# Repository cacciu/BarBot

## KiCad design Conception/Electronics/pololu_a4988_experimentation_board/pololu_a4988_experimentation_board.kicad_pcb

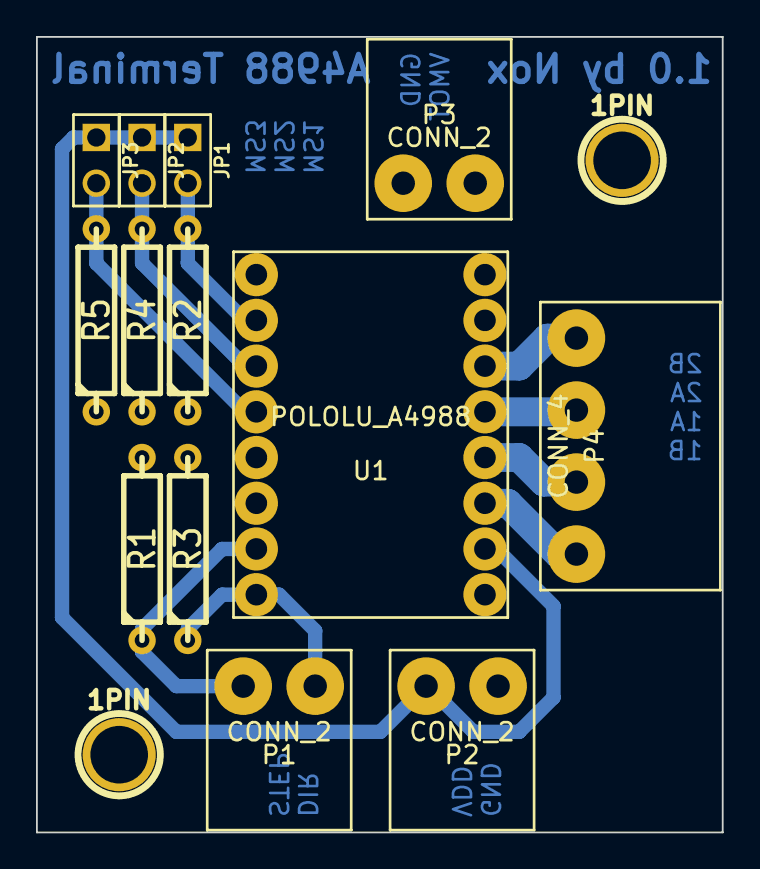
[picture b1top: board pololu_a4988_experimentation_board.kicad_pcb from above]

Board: 2 copper layers, 38.1 x 44.2 mm, 16 parts (1 on the bottom side), 12 nets.

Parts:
1PIN, 1PIN#2: P***; 1pin
C1: CP1; SMDSVP10
JP1, JP2, JP3: JUMPER; PIN_ARRAY_2X1
P1, P2, P3: CONN_2; Terminal2
P4: CONN_4; Terminal-4
R1, R2, R3, R4, R5: R; R4
U1: POLOLU_A4988; Pololu_A4988

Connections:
+24V: C1.1, P3.2, U1.16
GND: C1.2, P2.1, P3.1, R1.2, R2.1, R3.2, R4.1, R5.1, U1.1, U1.5, U1.6, U1.9, U1.15
unnamed: P4.2, U1.13
unnamed: P4.4, U1.11
unnamed: P4.3, U1.12
unnamed: P4.1, U1.14
unnamed: P1.1, R3.1, U1.8
unnamed: P1.2, R1.1, U1.7
unnamed: JP1.2, R2.2, U1.2
unnamed: JP3.2, R5.2, U1.4
unnamed: JP2.2, R4.2, U1.3
VDD: JP1.1, JP2.1, JP3.1, P2.2, U1.10

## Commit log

2015-04-28 Add first draft
2015-04-28 Add Readme
2015-07-05 Add Pump and Cup Dispenser Sketch
2015-07-06 Add tolerance for 3D printer
2015-07-06 Adapt Cup_Dispenser tolerances
2015-07-06 Adapt Hull to be better printable.
2015-07-06 Adapt 3d printing
2015-07-06 Adaption
2015-07-07 Add Slider Cover
2015-07-08 Adapt Hull to be easy printable
2015-07-09 Add a more dynamic version of Cup_Dispenser
2015-07-09 Add adaptive Cup Dispenser version
    Add new adaptive design for a wide span of cup sizes
2015-07-09 Adapt slider to include small chamfer on first ring
2015-07-12 Adapt Cup Dispenser slider to not squeeze cup
2015-07-13 Fix dependencies in Cup Dispenser
2015-07-14 Fix sizes, add board to cup dispenser
2015-07-14 Adapt pump adapter for servo test
2015-07-14 Adapt Pump Axes Adapter Holes
2015-07-15 Adapt hole sizes in Cup Designer, adapt axes
2015-07-16 Adapt Cup Dispenser Transmission Cage height
2015-07-17 Add chamfer for easy cup dispensing
2015-07-17 add bevel to slider separator
2015-07-17 Increase inner radius for better separation
2015-07-17 Increase only separator radius, chamfer on other ring
2015-07-19 Adapt Holes, Adapt Mount fixation point
2015-07-19 Add new cup dispenser concept
2015-07-20 Finish third gen cup dispenser design
2015-07-24 Add cutouts for wires to cup dispenser 3
2015-07-24 Add skrew hole to transmission
2015-07-24 Add Hull correction
2015-07-25 Resize the fixture for the PVC pipe
2015-07-29 Add Board Shape to Cup Dispenser
2015-07-29 Add Microswitch and LED holes to Cup Dispenser
2015-07-29 Resize RGB LED hole
2015-07-29 Redesign pump adapater, add chamfer to cup dispenser transmission
2015-07-29 Export STLs
2015-07-29 Add PCB project
2015-07-29 Fix bevel in cup dispenser transsmission
2015-07-30 Adaptable Pump Adapter Block
2015-07-30 Add Chamfer to Pump adapter block skrew holes
2015-07-30 Add chamfer to central axis of pump transmission
2015-07-30 Add Noah stuff
2015-07-30 Export STL
2015-07-31 Reduce tolerance of axis adapter
2015-07-31 Update Board
2015-08-03 Adapt cup dispenser board
    TODO:
    - motor connector
    - sensor (diodes, micro switch)
    -pulldowns for LED-driver connectors
2015-08-03 Update Axis and Transmission
2015-08-03 Widen transmission hole size. Bevel for more stability into projected form
2015-08-05 Adapt for Nema 11
2015-08-05 Adapt Board Cutout to include cable relaxation
2015-08-05 Finished schematics for cup dispenser board
    TODO:
    - route board
2015-08-08 Should be final schematic
    CHANGES:
    - added fill meter diode and endstop to connector bus
    - changed connector to wurth
    - started routing
    TODO:
    - route board
2015-08-09 Adapt Axis Adapter for better parametrization
2015-08-09 Adapt cup dispenser for nema 11 height. Add LED shift register stripe
2015-08-09 Cup Dispenser Fixture Montage larger
2015-08-09 Constrain to ground
2015-08-18 Add Transmission Nema 11 cut
2015-08-18 Widen Axis radius of transmission
2015-08-20 Fix transmission alignment
2015-08-20 Fix Hull alignment
2015-09-01 Update Board Layout
2015-09-01 Update Cup Dispenser Parts
2015-09-01 Update Cup Dispenser Parts 2
2015-10-01 Added basic firmware for CupDispenser board
2015-11-28 added PDF schematic for cup despenser board
2015-11-29 initial conept for ice dispenser, ready to print first parts A B
    A
2015-11-29 adding feed pipe for circular dispenser, minor fixes for main part
2016-01-04 added stray files for ice dispenser
2016-01-04 added one more lost file
2016-03-11 started test with auger style ice dispenser, parts are printing
2016-03-24 auger based ice dispenser elements resized for mounting inside 70mm tube
2016-04-08 Add ice crusher
2016-04-08 Add crusher claw step export
2016-04-08 Add new presentation
2016-04-12 Add Döme
2016-04-12 Adapt ice crusher
2016-04-15 Add new frame design
2016-04-26 New bigger crusher design
2016-04-29 First Scetch of the Barbot design
2016-05-03 Design: Minor Assembly changes
2016-05-10 Added Pump 3d model
2016-05-10 support arc
2016-05-13 Add a first draft of the sugardispenser.
    Use a screw conveyor-design to allow continuous
    dispension.
2016-05-23 TopArc Added
2016-05-24 Steckverbingungen und Assembly anpassungen
2016-05-26 Inventor Files converted to NX
2016-05-27 Pump parts fully converted to NX
2016-06-04 Pumpen Befestigung Kühlung
2016-10-31 Minor Arc inprovments, Pump Assembly
    hey
2016-11-15 The Brain
    half way done
2016-11-15 Start mit dem CAD Modell der Drehscheibe
2016-11-17 brain upper half almost done
2016-11-22 Kühlrippen an Pumpen
2016-11-22 Pumpen Befestigung
2016-11-22 adjustments to the brain, first look at pump positioning
2016-11-22 pump fixation
2016-11-24 Revert "brain upper half almost done"
    This reverts commit 4f98b2315e34f4146b362b8998b56d1d4f41124d.
2016-11-24 Update Funktionsscheibe
2016-12-01 Brain Backup
2016-12-06 Restdruckventil, Neue Ordnerstruktur
2017-02-16 Bohrlöcher Funktionsscheibe
2017-02-16 Wände des Funktionselements
2017-02-16 vergrösserung des Funktionselements
2017-02-16 Assemblz Funktionselement
2017-02-16 Finales Update für Heute
2017-02-21 Restdruckventil
2017-02-23 StepperControl
2017-02-24 Steppercontrol Update
2017-03-03 Cup Dispencer
2017-03-10 Update Steppercontrol
2017-03-17 Funktionselemt Assembly update
2017-03-17 Restdruckventil update
2017-03-17 Becherablage
2017-03-20 Update Stepperansteuerung
2017-03-24 Normenblatt BarBot
2017-03-24 Assembly Update
2017-03-24 Dokumentation Stepperdriver
2017-03-24 Schraubverbindungen
2017-03-29 Anpassung der Grösse der Führung
2017-03-29 Replace 001_000001_00_M_Standscheibe_unten.prt
2017-03-29 Replace 001_000001_00_M_Middle_Bottom.prt
2017-03-29 Anpassung der Dicke
2017-03-29 Working assembly
2017-03-29 Revert "Working assembly"
    This reverts commit f7fe3ca666919d35214edc5fb522ae36beaa3312.
2017-03-29 Revert "Anpassung der Dicke"
    This reverts commit c9ac998beea331d66196a48181d836443999247f.
2017-03-29 Revert "Replace 001_000001_00_M_Middle_Bottom.prt"
    This reverts commit 6c839cf3f9480c64a1d4dc5bc41729ec0b4781c2.
2017-03-29 Revert "Replace 001_000001_00_M_Standscheibe_unten.prt"
    This reverts commit 045dcf3bd6b367d9479cf99456941017bbd6bb16.
2017-03-29 erste hälfte Schraubverbindungen hinzugefügt
2017-03-30 Assemlbly Update
2017-03-30 Update Drehmechanismus
2017-03-31 Schraubverbindungen Teil2
2017-03-31 Übersicht über unseren Projektfortschritt
    Zum Ausfüllen und Weiterführen, damit wir wissen wo wir etwa stehen.
2017-03-31 Lasercutting instructions
2017-03-31 Updatew
2017-04-02 Führungsschiene für Becher
2017-04-03 Update Projektvortschritt
2017-04-03 Und nochmal :P
2017-04-03 Update Funktionselement
2017-04-03 LaserCutting Templates
2017-04-03 LaserCutting1
2017-04-03 Drawings fürs Lasercutten
2017-04-07 cup dispenser
    Becher Übergabe von Cup Dispenser zu Drehscheibe
2017-04-07 KiCad Ventilansteuerung
    Anfang des Ventilansteuerung PCB's
2017-04-07 Docus
    Ventilinsel in Docus
2017-04-07 KiCad Stepper
2017-04-07 Holding Mecanism
